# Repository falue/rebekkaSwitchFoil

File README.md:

# Art project with HLK-LD2450 Human detection sensor (Microwave-based)

This repo is using a HLK-LD2450 microwave human presence sensor and a [Sparkfun Thing Plus](https://www.sparkfun.com/products/15663). This uses Micropython. See below for instructions to set it up.

When at least one human being is in a pre defined target area in front of the sensor, a relay is triggered. In this application, this relay is wired to eg. a 30VAC source that switches off a PDLC foil (Polymer Dispersed Liquid Crystal) in front of a mirror.

Change the area in which the relay triggers in the `main.py` file:
```
p1 = (-66, 777)
p2 = (66, 777)
p3 = (35, 0)
p4 = (-35, 0)
```
Points clockwise, all values in cm.
Visualized and tested with script `_archive/tests/test-polygon-finder.py`.

Based on
- <https://github.com/christianDUCROS/ld2410-human_sensor>
- <https://github.com/QuirkyCort/IoTy/blob/main/public/extensions/ld2410.py>

# Sensor
Can be installed in case, but must have good wave transmission characteristics at 24 GHz and cannot contain metallic materials or materials that have a shielding effect on electromagnetic waves.

For example data and a lot more, check out the
[> HLK-LD2450-Instruction-Manual.pdf](docs/HLK-LD2450-Instruction-Manual.pdf).

## Sensor mounting direction

## Specs
|Key|Value|
|--|--|
|Max targets|3|
|ISM band|24 GHz|
|Detection distance|6m|
|Detection angle|±60°|
|Data per target|Xmm, Ymm, Speed mm/s|

> **Attention**:
> - Do not install multiple sensor directly opposite to each other to avoid mutual interference
> - Install 150cm to 200cm from floor

# SOFTWARE
## Micropython
### Firmware - once per device
Get <https://github.com/espressif/esptool>
First, erase flash memory from dir `esptool-maser`

```
cd _archive/esptool
esptool.py --port /dev/cu.usbserial-02762195 erase_flash
```

If:
```
A fatal error occurred: Could not open /dev/cu.usbserial-02762195, the port is busy or doesn't exist.
([Errno 16] could not open port /dev/cu.usbserial-02762195: [Errno 16] Resource busy: '/dev/cu.usbserial-02762195')
```
**Unconnect & reconnect**, immedietly run the command above again

Download generic firmware esp wroom:
- <https://micropython.org/download/#esp32>
- <https://micropython.org/download/ESP32_GENERIC/>

Eg. `v1.23.0 (2024-06-02) .bin`

Flash firmware:
```
esptool.py --chip esp32 --port /dev/cu.usbserial-02762195 --baud 460800 write_flash -z 0x1000 ESP32_GENERIC-20240602-v1.23.0.bin 
```

### To upload code
For vscode:
- pymakr extension install
- "new project" from sidebar
- `connect device` or three dots when hovering over project name `select devices`
- Click on the bolt on the device (if greyed out, right click three dots `stop script`)
- To upload click on "upload cloud" when hovering over device name
- After upload, three dots on device, `hard reset device`

> **Attention**
> - When changing the `pymakr.conf` file, its changes only take effect after its uploaded to the board. Right click on the `pymakr.conf` file > "pymakr" > "upload to device" before you upload the whole thing
> - When using "Development mode" (auto-upload files after each change), folders, subfolders and their content (like the `libraries`) do not get uploaded

### When in death loop
Delete main file directly on the flash memory:
- pip install oder so rshell & repl
- `rshell --port /dev/cu.usbserial-0275EAB2`
- `repl ~ /dev/cu.usbserial-0275EAB2`
- `ctrl+x = exit`
- `import os`
- `os.remove("main.py")`

# Pymakr.conf
Example:
```
{
  "py_ignore": [
    "_archive",
    "_tools",
    "docs",
    ".DS_Store",
    ".git",
    ".gitignore",
    ".gitmodules",
    ".vscode",
    "env",
    "README.md",
    "README.pdf",
    "venv"
  ],
  "name": "Rebekkas Smart Foil Extravaganza"
}
```

In terminal:
```
import os
os.listdir()
os.chdir("libraries")
```

### Interesting links from our research
- Library taken from https://github.com/QuirkyCort/IoTy/blob/main/public/extensions/ld2410.py
- Alternatively this french guy is using a similar or the same library:
    - https://www.youtube.com/watch?v=QDC7T2RiKgo
    - https://github.com/christianDUCROS/ld2410-human_sensor
- Arduino edition: https://github.com/0ingchun/arduino-lib_HLK-LD2450_Radar

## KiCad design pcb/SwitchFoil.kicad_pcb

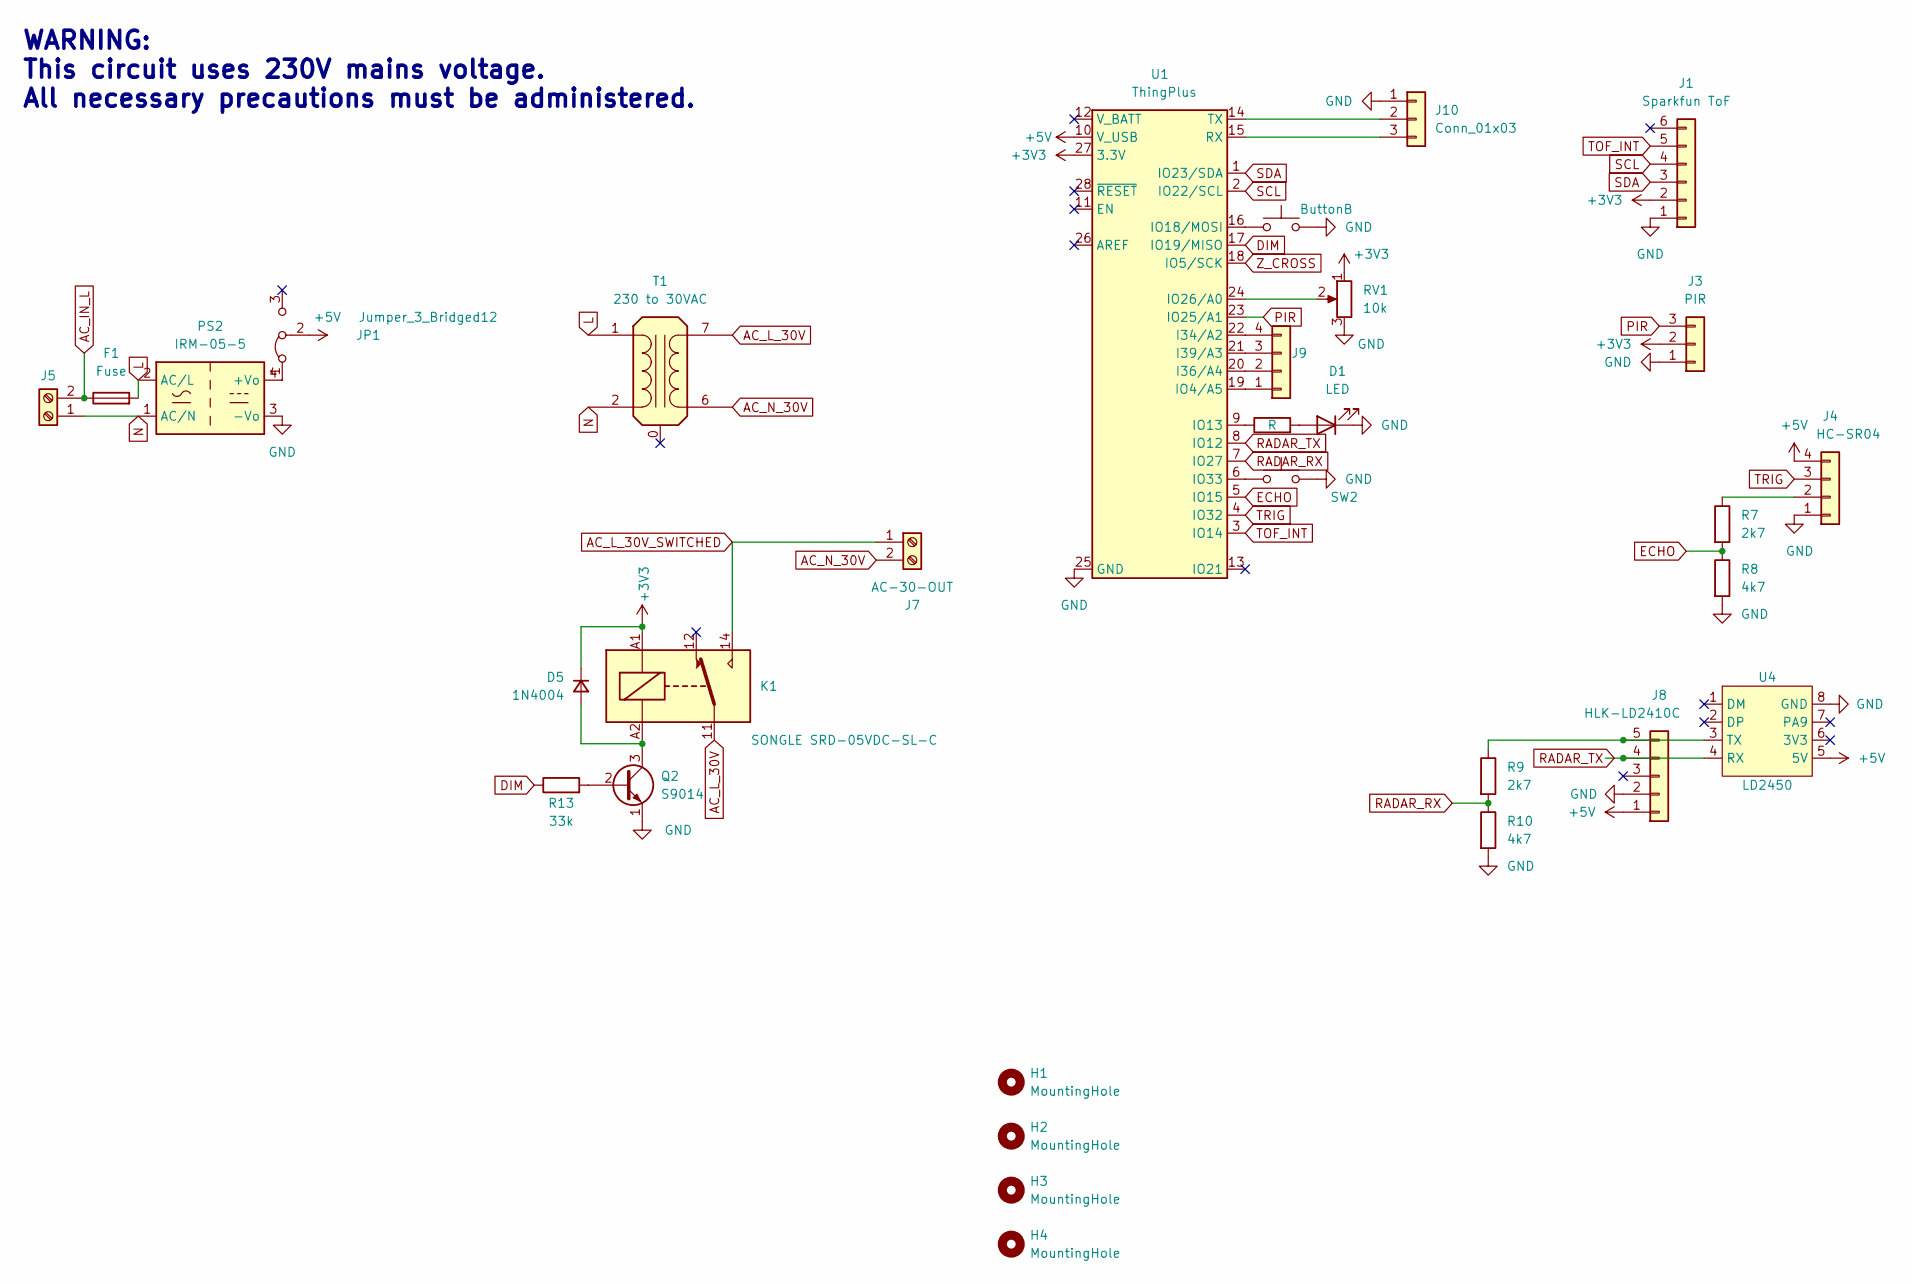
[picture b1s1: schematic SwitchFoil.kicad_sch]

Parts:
D1: LED; LED_D5.0mm
D5: 1N4004; D_A-405_P7.62mm_Horizontal
F1: Fuse; Fuseholder_Cylinder-5x20mm_Schurter_0031_8201_Horizontal_Op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
H1, H2, H3, H4: MountingHole; MountingHole_3.2mm_M3
J1: Sparkfun ToF; PinHeader_1x06_P2.54mm_Vertical
J3: PIR; PinHeader_1x03_P2.54mm_Vertical
J4: HC-SR04; PinHeader_1x04_P2.54mm_Vertical
J5: c8 inlet; c8-inlet-old
J7: AC-30-OUT; TerminalBlock_Phoenix_MKDS-1,5-2_1x02_P5.00mm_Horizontal
J8: HLK-LD2410C; PinHeader_1x05_P2.54mm_Vertical
J9: Conn_01x04; PinHeader_1x04_P2.54mm_Vertical
J10: Conn_01x03; PinHeader_1x03_P2.54mm_Vertical
JP1: Jumper_3_Bridged12; PinHeader_1x03_P2.54mm_Vertical
K1: SONGLE SRD-05VDC-SL-C; Relay_SPDT_Finder_36.11
PS2: IRM-05-5; Converter_ACDC_MeanWell_IRM-05-xx_THT
Q2: S9014; PinHeader_1x03_P2.54mm_Vertical
R1: R; R_Axial_DIN0207_L6.3mm_D2.5mm_P7.62mm_Horizontal
R7, R9: 2k7; R_Axial_DIN0207_L6.3mm_D2.5mm_P7.62mm_Horizontal
R8, R10: 4k7; R_Axial_DIN0207_L6.3mm_D2.5mm_P7.62mm_Horizontal
R13: 33k; R_Axial_DIN0207_L6.3mm_D2.5mm_P7.62mm_Horizontal
RV1: 10k; Potentiometer_Vishay_T73YP_Vertical
SW1: ButtonB; pts636
SW2: ButtonA; pts636
T1: 230 to 30VAC; Transformer_Myrra_EI30-5_44000_Horizontal
U1: ThingPlus; ThingPlus_With_Connectors
U4: LD2450; ld2450

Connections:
+3V3: D5.1 (K), J1.2, J3.2, K1.A1, RV1.1, U1.27 (3.3V)
+5V: J4.4, J8.1, JP1.2 (C), U1.10 (V_USB), U4.5 (5V)
AC_IN_L: F1.1, J5.2
AC_L_30V: K1.11, T1.7 (SB)
AC_L_30V_SWITCHED: J7.1, K1.14
AC_N_30V: J7.2, T1.6 (SA)
DIM: R13.1, U1.17 (IO19/MISO)
ECHO: R7.2, R8.1, U1.5 (IO15)
GND: D1.1 (K), J1.1, J3.1, J4.1, J8.2, J10.1, PS2.3 (-Vo), Q2.1 (E), R8.2, R10.2, RV1.3, SW1.2, SW2.2, U1.25 (GND), U4.8 (GND)
L: F1.2, PS2.2 (AC/L), T1.1 (AA)
N: J5.1, PS2.1 (AC/N), T1.2 (AB)
unnamed: D1.2 (A), R1.2
unnamed: D5.2 (A), K1.A2, Q2.3 (C)
unnamed: J4.2, R7.1
unnamed: J8.5, R9.1, U4.3 (TX)
unnamed: J9.1, U1.19 (IO4/A5)
unnamed: J9.2, U1.20 (I36/A4)
unnamed: J9.3, U1.21 (I39/A3)
unnamed: J9.4, U1.22 (I34/A2)
unnamed: J10.2, U1.14 (TX)
unnamed: J10.3, U1.15 (RX)
unnamed: JP1.1 (A), PS2.4 (+Vo)
unnamed: Q2.2 (B), R13.2
unnamed: R1.1, U1.9 (IO13)
unnamed: SW1.1, U1.16 (IO18/MOSI)
unnamed: RV1.2, U1.24 (IO26/A0)
unnamed: SW2.1, U1.6 (IO33)
PIR: J3.3, U1.23 (IO25/A1)
RADAR_RX: R9.2, R10.1, U1.7 (IO27)
RADAR_TX: J8.4, U1.8 (IO12), U4.4 (RX)
SCL: J1.4, U1.2 (IO22/SCL)
SDA: J1.3, U1.1 (IO23/SDA)
TOF_INT: J1.5, U1.3 (IO14)
TRIG: J4.3, U1.4 (IO32)
Z_CROSS: U1.18 (IO5/SCK)

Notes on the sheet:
WARNING: This circuit uses 230V mains voltage. All necessary precautions must be administered.

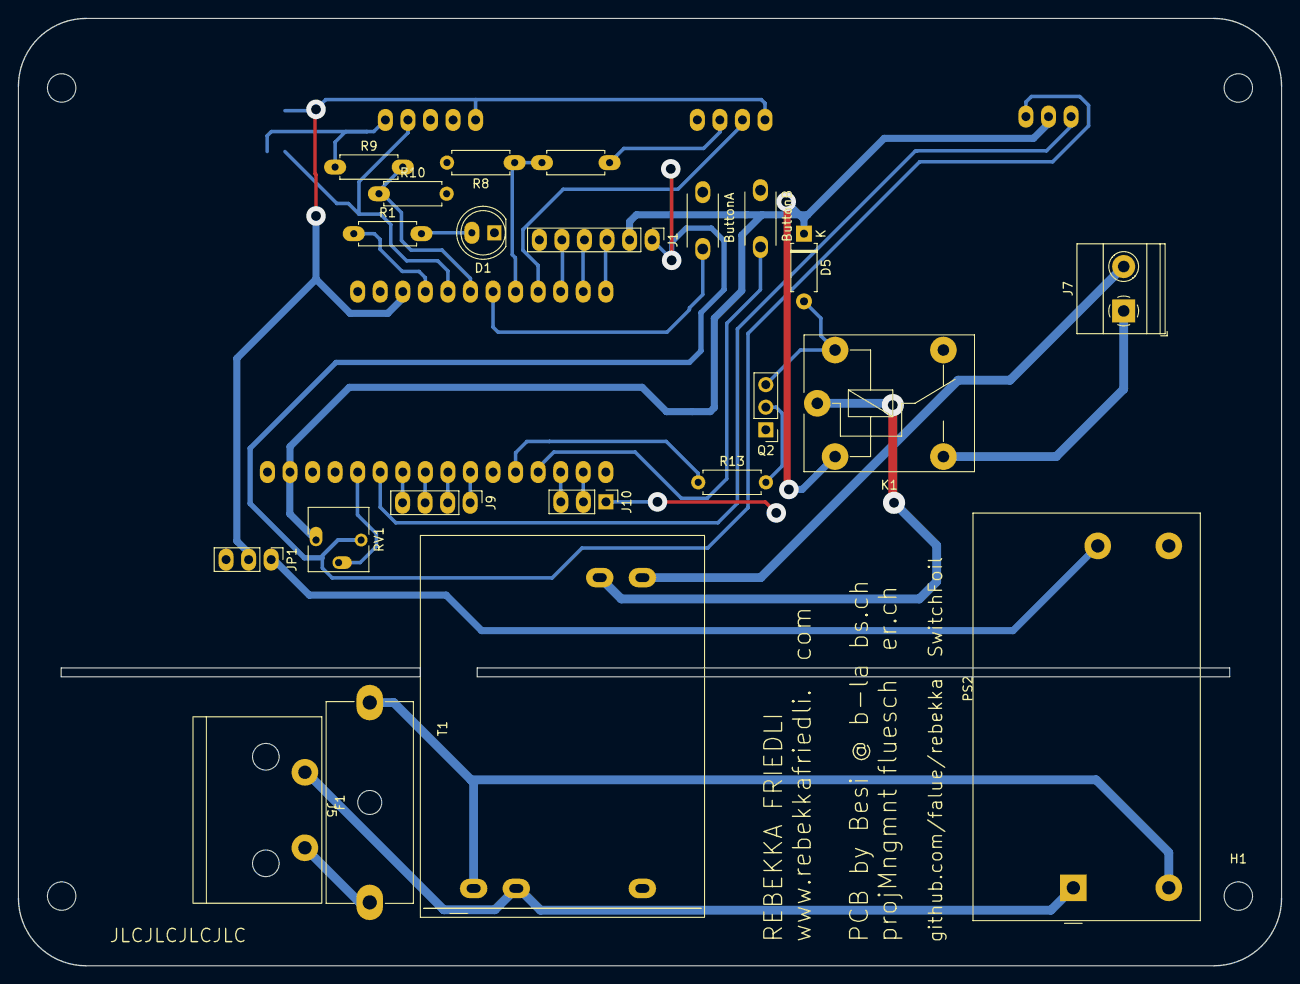
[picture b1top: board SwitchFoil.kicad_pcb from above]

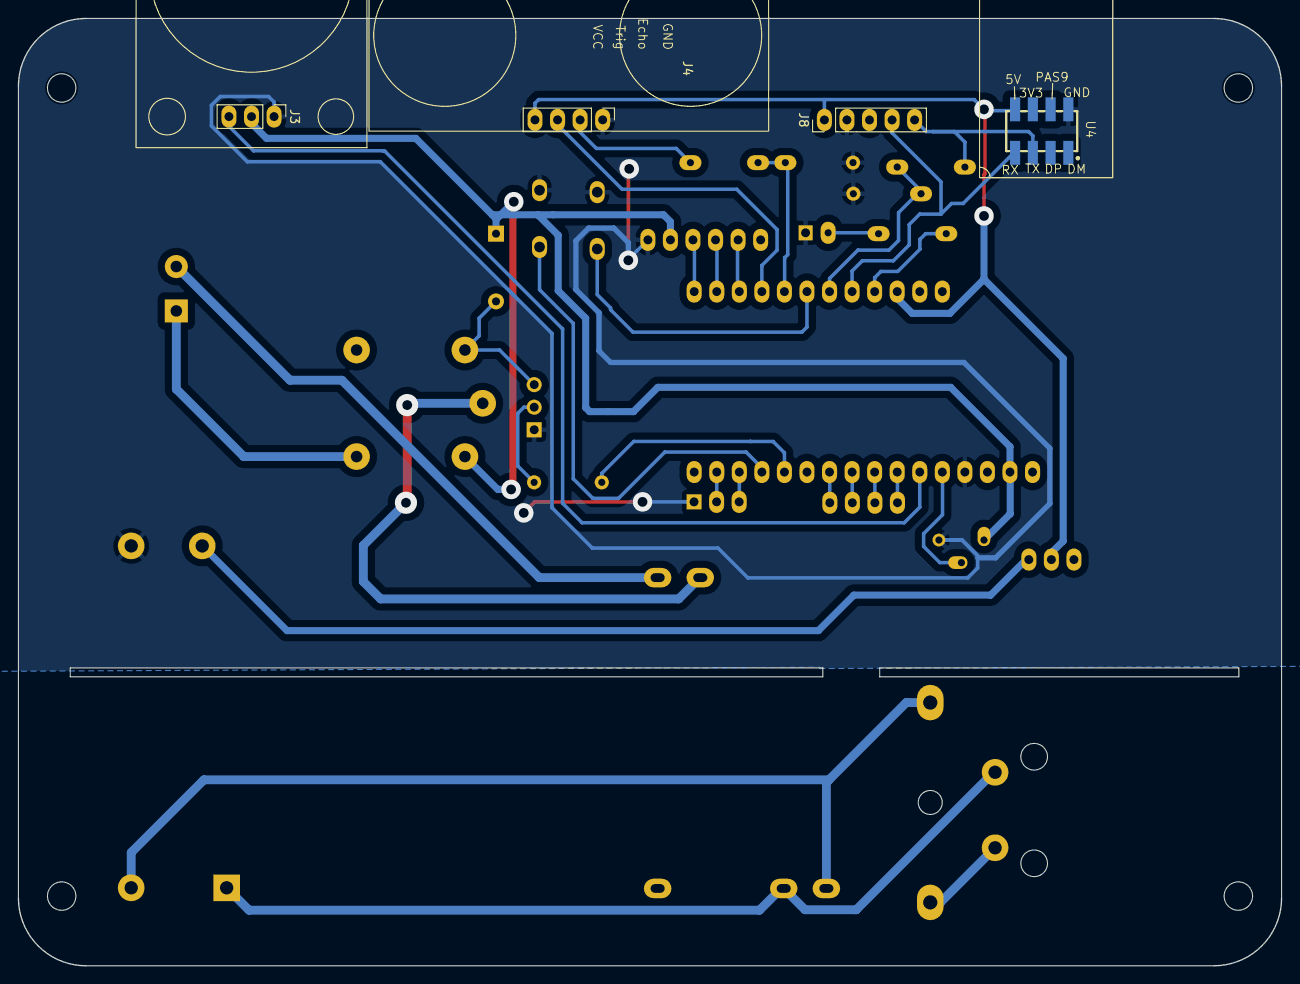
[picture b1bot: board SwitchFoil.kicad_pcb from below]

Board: 2 copper layers, 142.2 x 106.7 mm, 31 parts (4 on the bottom side), 34 nets.

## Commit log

2023-12-07 Add readme, shuffle things around
2024-03-01 Add ground truth; some butchering of everything
2024-03-01 Get rid of some profanity
2024-04-02 Add archive
2024-04-02 gewurstel
2024-04-12 Add PCB
2024-04-12 Add hcsr04 library
2024-04-12 The problem was a wiring issue and not related to code
2024-04-12 Add radar connector (currently using the same pins as HC-SR04)
2024-04-12 Add radar test code which currently fails
    See christianDUCROS/ld2410-human_sensor#1
2024-04-16 Rudimentary radar detection
2024-04-17 Add 30VAC transformers and Dimmer plus ugly routing to get a sense of the positions
2024-04-17 Dimmer code
2024-04-17 Dimmer as library
2024-04-18 Update pcb
2024-04-19 Add LD2450 socket
2024-04-19 Prepare for milling
2024-04-19 Small PCB improvements
    Point the C8 plug downwards
    Bigger holes for the fuse holder
2024-04-19 New pinout
2024-04-19 Move compoenents to the very edge
2024-04-21 Update pinout of esp32 thing plus
2024-04-23 Fix dimmer code
2024-04-23 Make a non 60VAC pcb but use the dimmer to regulate the voltage
2024-04-23 Final tweaks for the 230VAC-only pcb
2024-04-24 Add 5V Jumper and slightly extend the screw terminals for the dimmer
2024-04-24 Add main script to test the dimmer cycling through 10% steps of the dimmer value
2024-04-24 Add 5V jumper and extended dimmer footprint
2024-04-24 Use the small c8 power outlet
2024-05-01 Add power resistors for limiting the current and for potentially lowering the output AC voltage
2024-05-14 add plans
2024-05-14 set correct dotted lines
2024-05-14 correct measurements
2024-05-21 Add prices to schematic’s BOM
2024-05-24 Prepare for JLC manufacturing
    - Remove one of the 30VAC transformers
    - Remove the dimmer
    - Already added the relay for switching on the 30VAC
2024-05-26 Remove plans
2024-05-26 Move mounting holes and use available space in box
2024-05-26 Do not ignore gerber plot output
2024-05-26 Add gerber & drill export files
2024-05-26 Layer selection for export is saved in files, apparently
2024-05-29 Changes according to questions regarding the final JLC design
2024-05-31 Add URLs of critical components
2024-06-04 Add code for person sensor
2024-06-04 Add radar notes
2024-06-04 Add HLK-LD2450 instruction manual
2024-06-04 Alternative for dimming 230V (untested)
2024-06-04 Test the buttons
2024-06-04 Add ESP32 Thing Plus pinout
2024-06-10 Adjsut layout for print
2024-06-13 First version
2024-06-14 Next iteration
2024-06-14 Add LED blink script
2024-06-14 add micropython sketch
2024-06-14 new notes
2024-06-14 Move libraries
2024-06-15 Restructure project
2024-06-15 revert to working state
2024-06-15 Some experiments
2024-06-15 add test function for finding point inside form
2024-06-15 Rename local vars to not confuise globals
2024-06-16 keep old version
2024-06-16 Re-add esptool for initial flashing
2024-06-16 Add visualisation to test
2024-06-16 Test and visualize up to three targets
2024-06-16 make interactive
2024-06-16 Do not crash on window close; keep window alive; animate targets
2024-06-16 More exciting movements
2024-06-16 Use cm; more realisitc poligon shape for project
2024-06-16 Basic readme
2024-06-17 first dalius version
2024-06-17 first working version
2024-06-19 add pcb again
2024-06-20 Ignore backup files
2024-06-20 Faster flashing
2024-06-20 Match polygon to rebekkas desire
2024-07-02 add visualization to readme
2024-07-02 re-center target space
2024-07-02 redefine pins for testing
2024-07-10 Ignore pcb when uploading
2024-08-12 invert logic
2024-08-12 Make better for debugging
